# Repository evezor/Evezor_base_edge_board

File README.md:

# Evezor Edge Base Board
An edge board with only base functionality. Conatains, heartbeat LED, neopixel status light, function button, power regulation, Evezor Microcontroller Unit and standard communication connectors in a standard layout.

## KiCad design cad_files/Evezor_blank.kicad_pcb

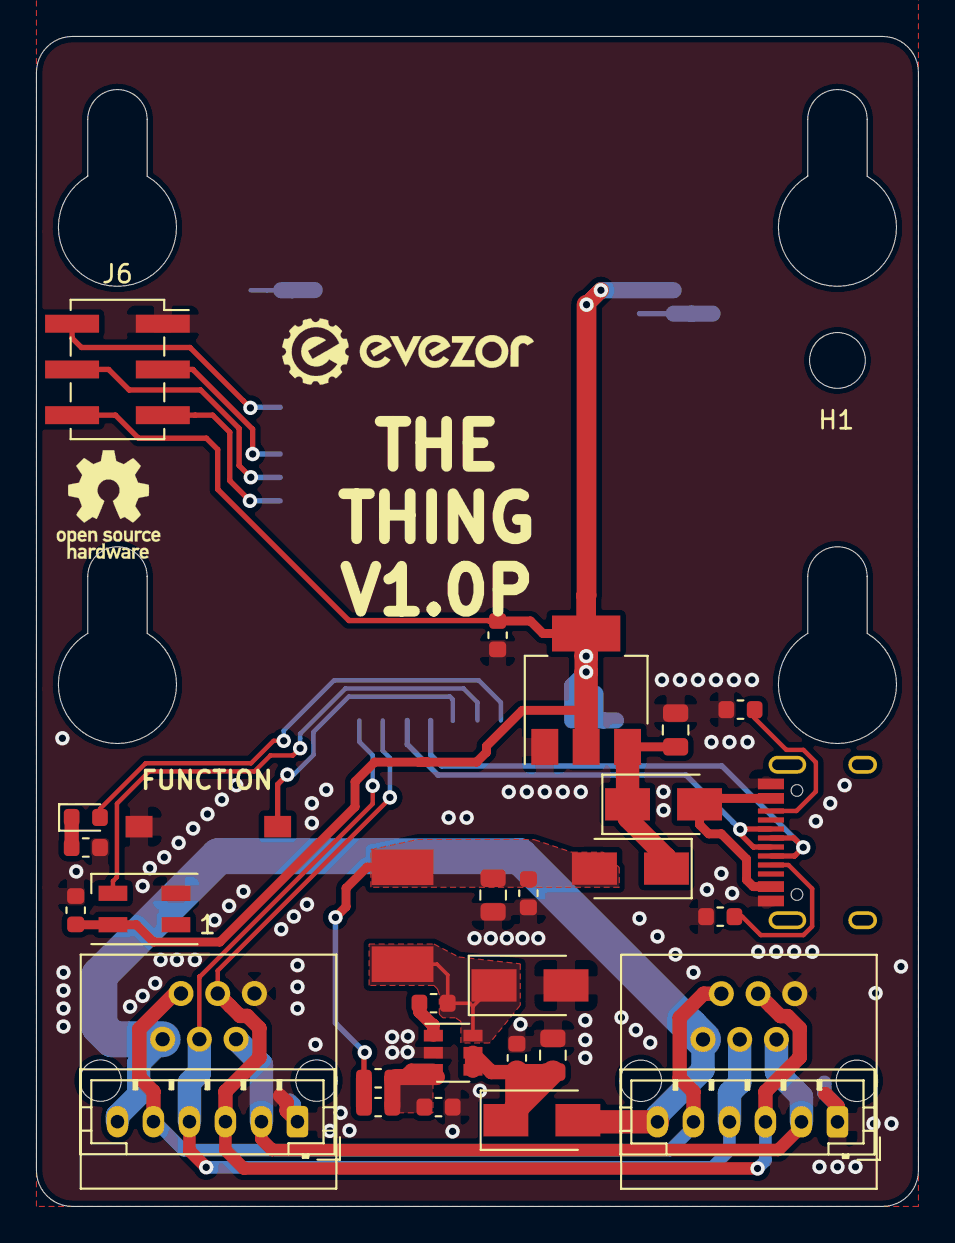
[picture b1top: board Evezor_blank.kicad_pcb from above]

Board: 2 copper layers, 49.0 x 65.0 mm, 32 parts (1 on the bottom side), 26 nets.

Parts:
C1, C2, C3, C5, C10: .1uF; C_0603_1608Metric
C4: 4.7uF; C_0805_2012Metric
C6: 22uF; C_0805_2012Metric
C8: 10uF; C_0805_2012Metric
C9: C_Small; C_0603_1608Metric
D1, D2, D4, D5: SX35_SCHOTTKY; D_SMA
D3: LED; LED_0603_1608Metric
D6: SK6812MINI; LED_SK6812MINI_PLCC4_3.5x3.5mm_P1.75mm
H1: MountingHole; OLED_STANDOFF
J1: USB_C_Receptacle_USB2.0; USB_C_Receptacle_HRO_TYPE-C-31-M-12
J2, J3: RJ11; RJ11_C189747_Horizontal
J4, J5: PH; JST_PH_B6B-PH-K_1x06_P2.00mm_Vertical
J6: Conn_02x03_Odd_Even; PinSocket_2x03_P2.54mm_Vertical_SMD
L1: 22uH; INDUCTOR_7.5X6.6_GCDA0630-220MC
R1, R5: 15k; R_0603_1608Metric
R2: 82k; R_0603_1608Metric
R3, R4: 5.1k; R_0603_1608Metric
SW1: SW_Push; SWITCH_2x3_SMD_TACTILE_GREEN
U1: SY8401ABC; SOT-23-6
U2: AMS1117-3.3; SOT-223-3_TabPin2
U3: EDGE_STM32F405_CPU_V1; EDGE_STAMP

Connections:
+3V3: C9.2, C10.1, D6.4, J6.6, U2.2, U3.1, U3.18
/BOOT: J6.3, U3.36
/CAN_H: J2.3, J3.3, J4.3, J5.3, U3.26
/CAN_L: J2.4, J3.4, J4.4, J5.4, U3.27
/CC1: J1.A5, R4.1
/CC2: J1.B5, R3.1
/D+: J1.A6, J1.B6, U3.25
/D-: J1.A7, J1.B7, U3.24
/FD_H: J2.2, J3.2, J4.2, J5.2
/FD_L: J2.5, J3.5, J4.5, J5.5
/FUNCTION_BUTTON: SW1.1, U3.23
/HBT_LED: D3.2, U3.21
/NEO_STATUS: D6.3, U3.22
/OLED_SCL: J6.5, U3.34
/OLED_SDA: J6.4, U3.35
/RESET: J6.2, U3.38
/USB_VCC: D4.2, J1.A4, J1.A9, J1.B4, J1.B9
/VREG_OUT: C2.1, C5.1, C6.1, D5.2, L1.2, R2.1
GND: C3.2, C4.2, C5.2, C6.2, C8.2, C9.1, C10.2, D1.2, D6.2, J1.A1, J1.A12, J1.B1, J1.B12, J2.1, J3.1, J4.1, J5.1, J6.1, R1.1, R3.2, R4.2, R5.1, SW1.2, U1.2, U2.1, U3.2, U3.17, U3.43
unnamed: C1.1, D1.1, L1.1, U1.6
unnamed: C1.2, U1.1
unnamed: C2.2, R1.2, R2.2, U1.3
unnamed: C3.1, C4.1, D2.1, U1.4, U1.5
unnamed: C8.1, D4.1, D5.1, U2.3
unnamed: D3.1, R5.2
VBUS: D2.2, J2.6, J3.6, J4.6, J5.6

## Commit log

2020-11-06 first
2020-11-06 resync
2020-11-29 clean up fab layer
